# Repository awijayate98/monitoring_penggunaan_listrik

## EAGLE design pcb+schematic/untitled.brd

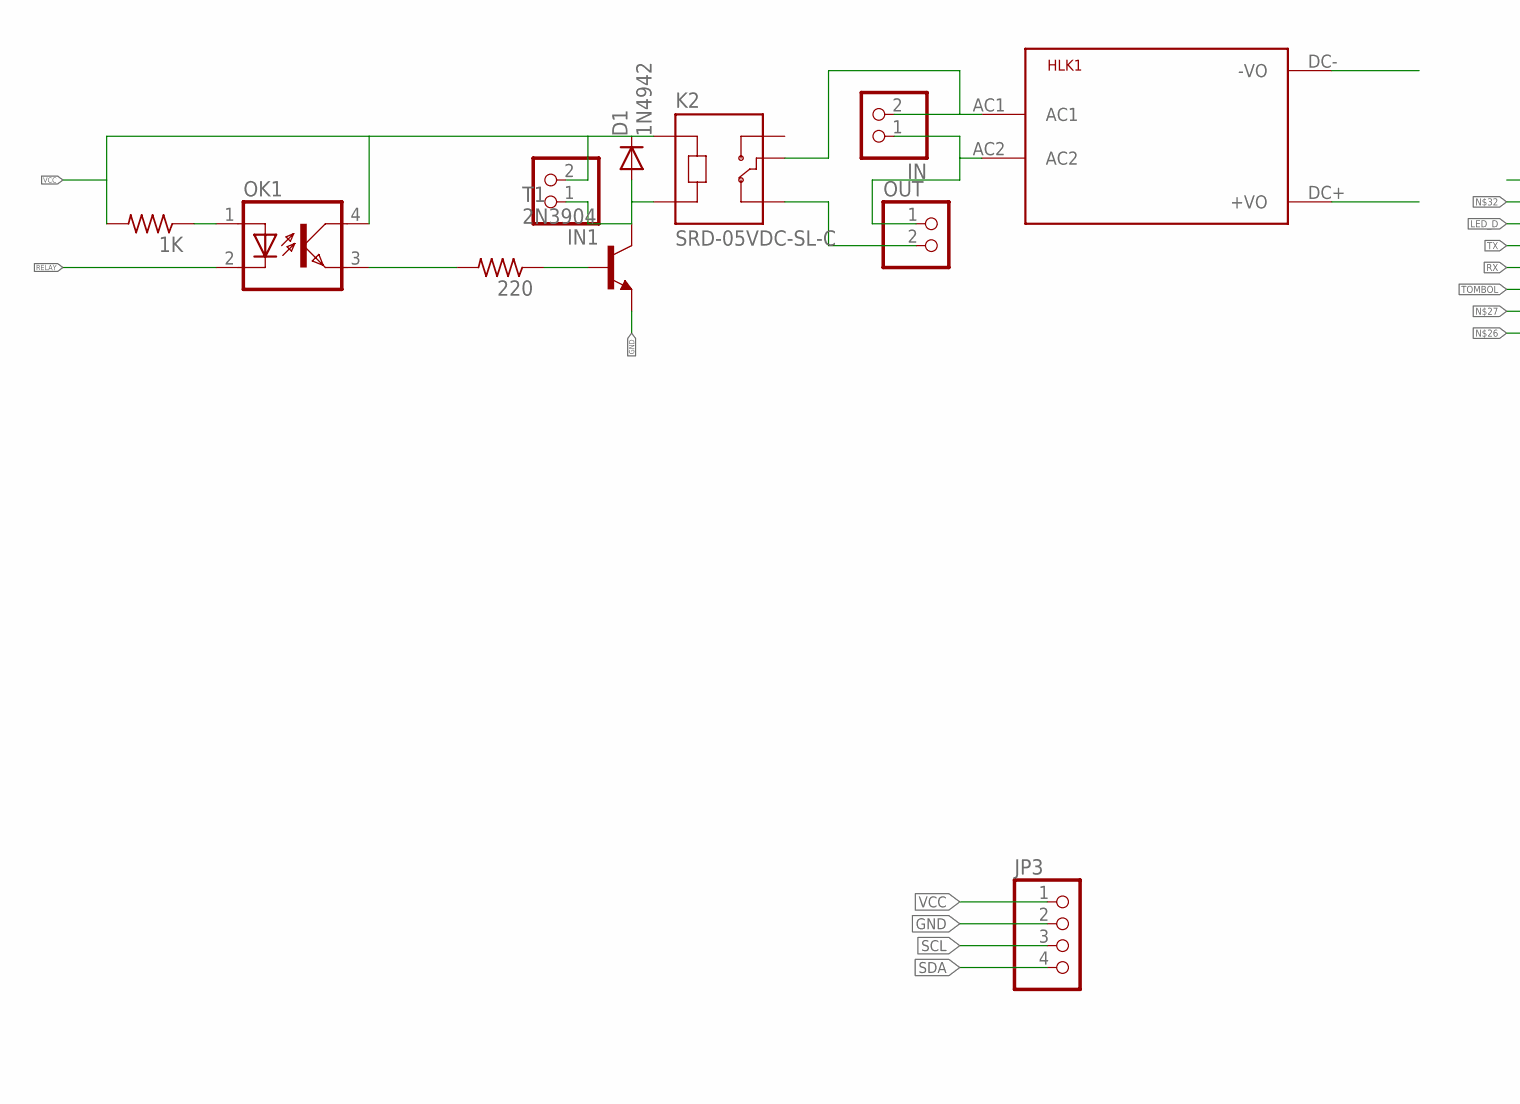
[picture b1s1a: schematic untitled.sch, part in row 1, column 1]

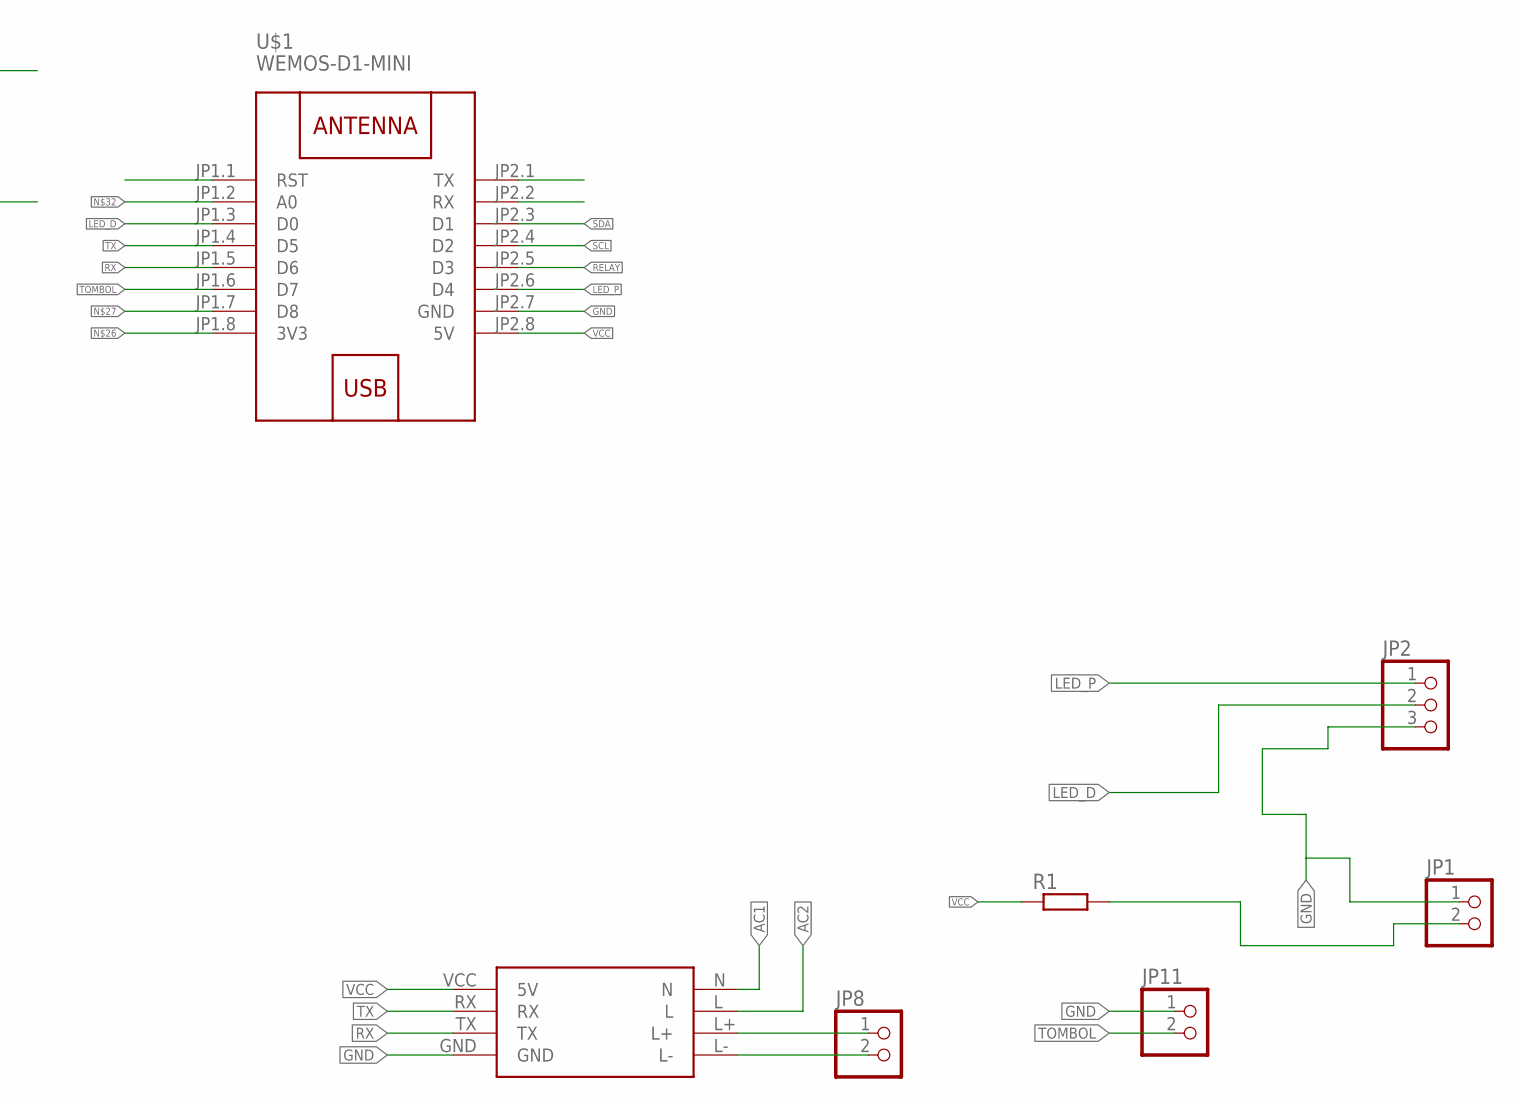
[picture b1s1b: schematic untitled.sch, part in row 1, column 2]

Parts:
1K, 220: R-US_0204/7; 0204/7
D1: 1N4942; DO41-10
HLK1: HLK-PM013W; HLK-PM01
IN, IN1: PINHD-1X2; 1X02
JP1, JP8, JP11: PINHD-1X2; 1X02
JP2: PINHD-1X3; 1X03
JP3: PINHD-1X4; 1X04
K2: SRD-05VDC-SL-C; RELAY_SRD-05VDC-SL-C
OK1: PC817; DIL04
OUT: PINHD-1X2; 1X02
R1: R-EU_0204/7; 0204/7
T1: 2N3904; TO92
U$1: WEMOS-D1-MINI
U$2: PZEM004T

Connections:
AC1: HLK1.AC1, IN.2, K2.COM, U$2.N
AC2: HLK1.AC2, IN.1, OUT.1, U$2.L
GND: HLK1.DC- (-VO), JP1.1, JP2.3, JP3.2, JP11.1, T1.3 (E), U$1.JP2.7 (GND), U$2.GND
LED_D: JP2.2, U$1.JP1.3 (D0)
LED_I: JP1.2, R1.2
LED_P: JP2.1, U$1.JP2.6 (D4)
unnamed: JP8.1, U$2.L+
unnamed: JP8.2, U$2.L-
unnamed: 220.2, OK1.3 (EMIT)
unnamed: 1K.1, OK1.1 (A)
unnamed: D1.A, IN1.1, K2.A2, T1.1 (C)
unnamed: 220.1, T1.2 (B)
unnamed: K2.NC, OUT.2
RELAY: OK1.2 (C), U$1.JP2.5 (D3)
RX: U$1.JP1.5 (D6), U$2.TX
SCL: JP3.3, U$1.JP2.4 (D2)
SDA: JP3.4, U$1.JP2.3 (D1)
TOMBOL: JP11.2, U$1.JP1.6 (D7)
TX: U$1.JP1.4 (D5), U$2.RX
VCC: 1K.2, D1.C, HLK1.DC+ (+VO), IN1.2, JP3.1, K2.A1, OK1.4 (COL), R1.1, U$1.JP2.8 (5V), U$2.VCC (5V)

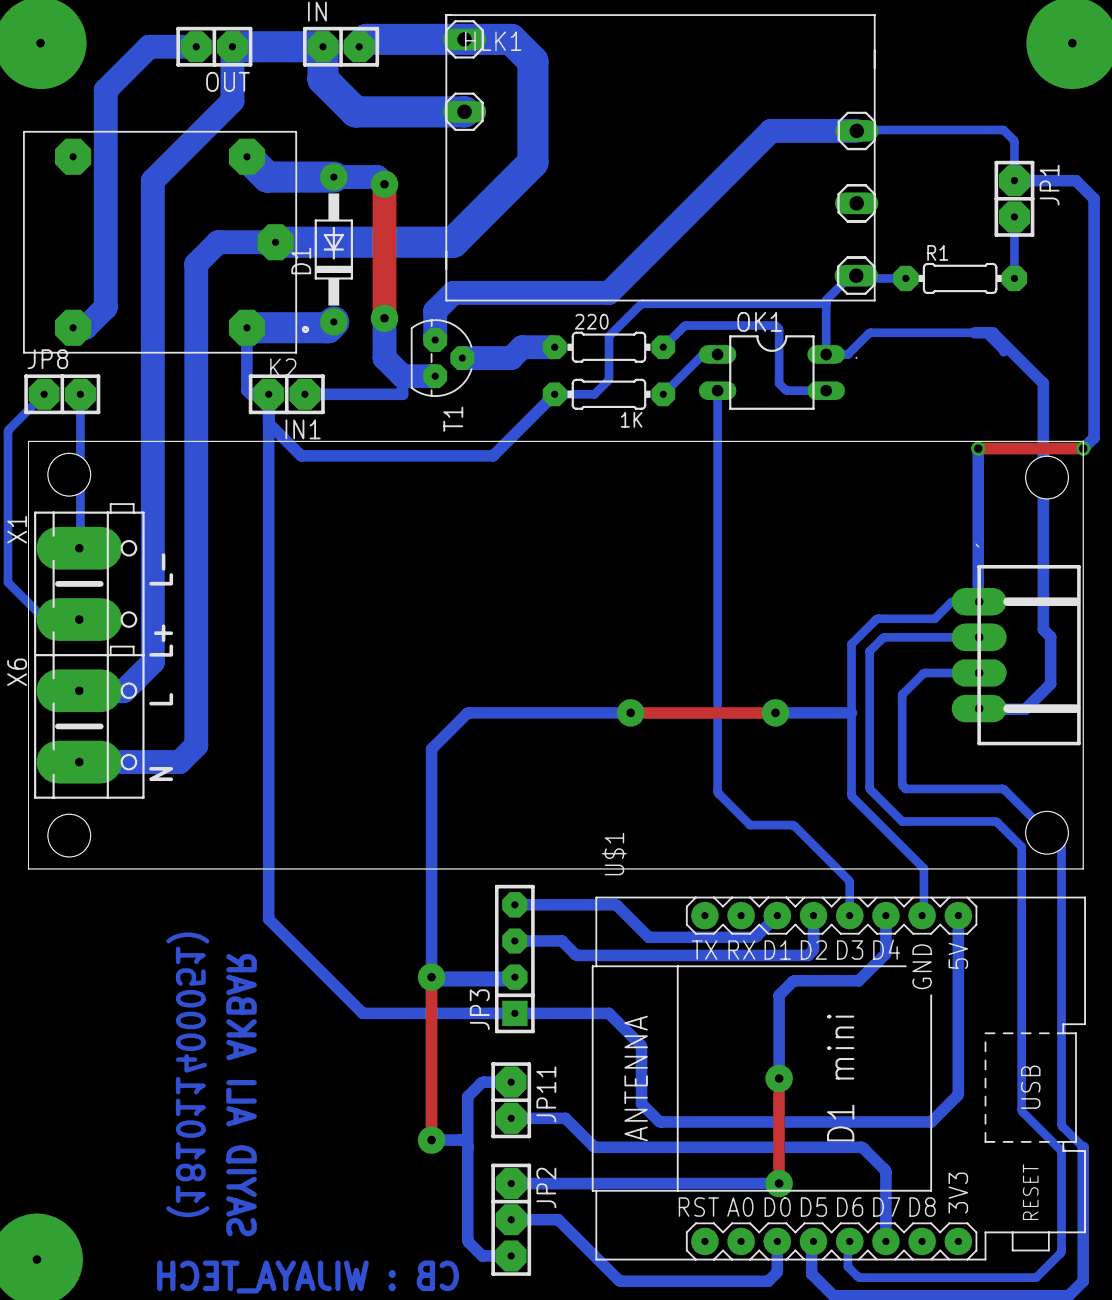
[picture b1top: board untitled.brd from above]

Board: 2 copper layers, 18 parts (0 on the bottom side), 20 nets.

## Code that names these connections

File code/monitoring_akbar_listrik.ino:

/* PIN CONFIGURATION 
 *  PZEM004T RX  -> D5
 *           TX  -> D6
 *  LCD I2C  SCL -> D2
 *           SDA -> D1
 *  LED_K_D  C   -> D3
 *  LED_K_P  C   -> D4
 *  RELAY    IN  -> D0
 *  TMBL_R   IN  -> D7
 *  
 *  
 */

#define BLYNK_PRINT Serial
#include <PZEM004Tv30.h>
#include <SoftwareSerial.h>
#include <Wire.h> 
#include <LiquidCrystal_I2C.h>
#include <ESP8266WiFi.h>
#include <BlynkSimpleEsp8266.h>
#include <ArduinoJson.h>
#include <FS.h>
#include <WiFiManager.h>
#include <ESP8266mDNS.h>
#include <WiFiUdp.h>
#include <ArduinoOTA.h>

#define relay D3
#define led_d D0
#define led_p D4
#define tombol_r D7
#define ditekan 0
#define l_hidup 1
#define l_mati 0
#define simpan_wifi 1
#define simpan_data 2

char blynk_token[34] = "VTup7n_iy1rxwsavXQSYUMno0Qilel66";
char blynk_host[20] = "blynk.iot-cm.com";
char blynk_port[7] = "8080";
char g_listrik[15] = "1.444.70";
int portblynk= 8080;
bool shouldSaveConfig = false;

float kal;
int golongan_listrik;
float b_gl;
float voltage, current, power, energy,frequency;
float cost_kwh;
float Wattage;
int mVperAmp = 66; // use 185 for 5A, 100 for 20A Module and 66 for 30A Module
double Voltage = 0;
double VRMS = 0;
double AmpsRMS = 0;
int flag;
int a,b;
boolean cutoff = false;
String kalimat, statusalat;
String statusl;
int waktu_sebelumnya = 0;
String api_key = "tPmAT5Ab3j7F9";
byte ring = 0;
int model;
boolean kondisi_reset = false;

BlynkTimer timer;
WidgetTerminal terminal(V7);
SoftwareSerial pzemSWSerial(D5, D6);
PZEM004Tv30 pzem_f(pzemSWSerial);
LiquidCrystal_I2C lcd(0x3F, 16, 2);
WiFiManager wifiManager;


void setup() {  //fungsi utama setup yannge berjalan hanya sekali ketika alat di hidupkan pada arduino
  Serial.begin(115200);
  WiFi.mode(WIFI_STA);
  pinMode(tombol_r, INPUT_PULLUP);
  pinMode(led_d, OUTPUT);
  pinMode(led_p, OUTPUT);
  pinMode(relay, OUTPUT);
  digitalWrite(led_p, LOW);
  lcd.begin();
  lcd.backlight();
  lcd.setCursor(0,0);
  lcd.print("MONITORING LISTRIK");
  delay(1000);
  lcd.clear();
  WiFi.begin(WiFi.SSID().c_str(), WiFi.psk().c_str());
  if (!wifiManager.autoConnect("Air Quality", "12345678")) {
    Serial.println("failed to connect and hit timeout");
    delay(3000);
    ESP.reset();
    delay(3000);
  }
  inisial_ota();
  byte kondisi_tombol = digitalRead(tombol_r);
  if(kondisi_tombol == ditekan && kondisi_reset == false)
  {
    kondisi_reset = true;
    delay(200);
  }
    while(kondisi_reset == true)
    {
      ArduinoOTA.handle();
      lcd.setCursor(0,0);
      lcd.print("MODE PROGRAM");
    Serial.println("MODE PROGRAM");
  }
  initialize();
  kondisi(l_hidup);
  Blynk.begin(blynk_token, WiFi.SSID().c_str(), WiFi.psk().c_str(),blynk_host,portblynk);
  timer.setInterval(1000L, kirimdata);
  lcd.clear();
  Blynk.run();
  Blynk.virtualWrite(V8, model);
  //delay(2000);
  kondisi_reset = false;
}  

void loop() {  //fungsi utama looping pada arduino
  ArduinoOTA.handle();
  Blynk.run();
  timer.run();
  bacasensor();
  tampil_lcd();
  tampilserial();
  kirimdata();
  if(digitalRead(tombol_r) == ditekan && kondisi_reset == false)
  {
    ESP.reset();
  }
}

void kirimdata(){ //fungsi untuk mengirim data ke blynk
  Blynk.virtualWrite(V0, voltage);
  Blynk.virtualWrite(V1, current);
  Blynk.virtualWrite(V2, power);
  Blynk.virtualWrite(V3, energy);
  Blynk.virtualWrite(V4, frequency);
  Blynk.virtualWrite(V6, cost_kwh);
  terminal.println(kalimat);
  digitalWrite(led_d, HIGH);
  delay(100);
  digitalWrite(led_d, LOW);
  delay(100);
}

  BLYNK_WRITE(V8)
{   
  kondisi(param.asInt());
}


  BLYNK_WRITE(V10)
{   
 lcd.setCursor(0,0);
 lcd.print("MEMFORMAT DATA WIFI ");
 wifiManager.resetSettings();
 delay(500);
 SPIFFS.format();
 delay(500);
 delay(500);
 ESP.reset();
}

  BLYNK_WRITE(V9)
{   
 lcd.setCursor(0,0);
 lcd.print("MEMFORMAT DATA ENERGY ");
  delay(3000);
  pzem_f.resetEnergy();
 delay(500);
 ESP.reset();
}


void kondisi(byte i) //fungsi untuk menghidupkan dan mematikan listrik perintah dari blynk
{
  
  if (i == l_hidup)
  {
    statusl = "LISTRIK HIDUP";
    digitalWrite(relay, LOW);
    model = 1;
  }else if(i == l_mati)
  {
    statusl = "LISTRIK MATI";
    digitalWrite(relay, HIGH);
    model = 0;
  }
}

void bacasensor() //fungsi membaca sensor
{
  if(isnan(pzem_f.voltage())){
    Serial.println("BACA ");
  }else{
    voltage = pzem_f.voltage();
    current = pzem_f.current();
    power = pzem_f.power();
    energy = pzem_f.energy(), 3;
    frequency = pzem_f.frequency();
    cost_kwh = energy * atof(g_listrik); 
  }
}

void tampilserial() { //fungsi untuk menampilkan serial
    kalimat = "volt=";
    kalimat += voltage;
    kalimat += "&";
    kalimat += "frek=";
    kalimat += frequency;
    kalimat += "&";
    kalimat += "amper=";
    kalimat += current;
    kalimat += "&";
    kalimat += "watt=";
    kalimat += power;
    kalimat += "&";
    kalimat += "status=";
    kalimat += statusl;
    kalimat += "&";
    kalimat += "kwh=";
    kalimat += energy;
    kalimat += "&";
    kalimat += "biaya=";
    kalimat += "RP. ";
    kalimat += cost_kwh;
    Serial.println(kalimat);

}

void tampil_lcd() { //fungsi untuk menampilkan pada lcd

  lcd.clear();
  lcd.setCursor(0, 0);
  lcd.print("V:");
  lcd.print(voltage);

  lcd.setCursor(9,0);
  lcd.print("P:");
  lcd.print(power);

  //baris 2
  lcd.setCursor(0, 1);
  lcd.print("A:");
  lcd.print(current);
  
  lcd.setCursor(9, 1);
  lcd.print("E:");
  lcd.print(energy);
}

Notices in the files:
parts and their libraries:
diy-modules: Released under the Creative Commons Attribution 4.0 International License: http://creativecommons.org/licenses/by/4.0
